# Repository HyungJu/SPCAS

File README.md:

# SPCAS
SmartPencilCase Application, PCB Design

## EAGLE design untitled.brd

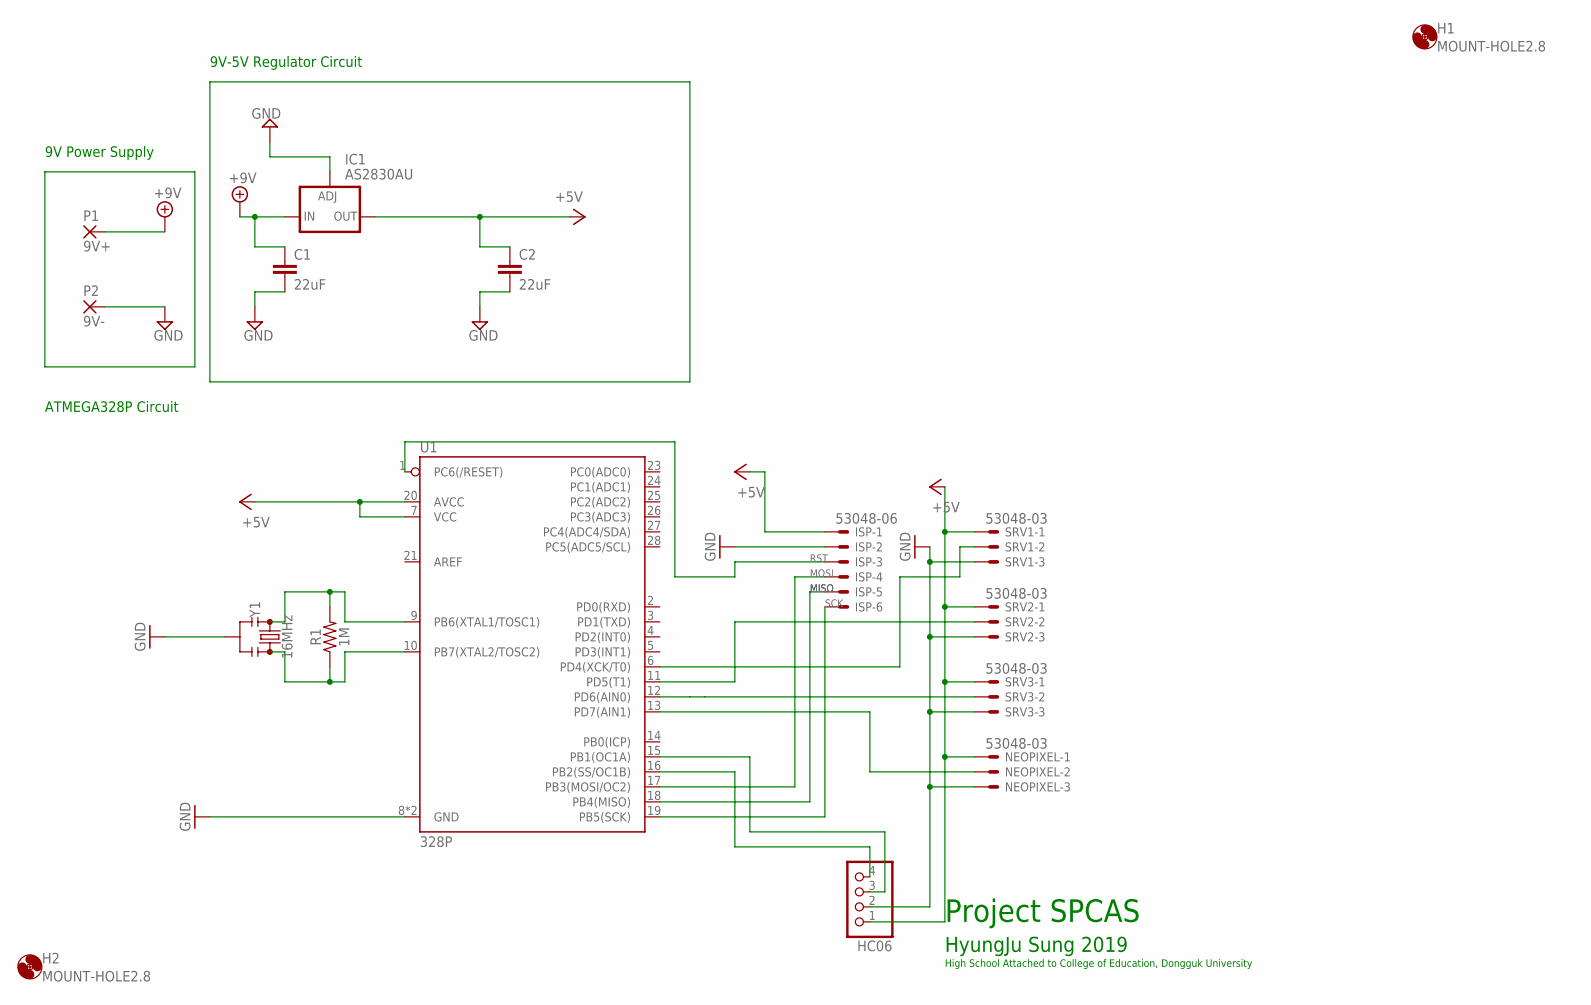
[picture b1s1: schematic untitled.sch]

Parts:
C1, C2: 22uF; C2.5-2
H1, H2: MOUNT-HOLE2.8; 2,8
HC06: PINHD-1X4/90; 1X04/90
IC1: AS2830AU; 337TL
ISP: 53048-06
NEOPIXEL: 53048-03
P1: 9V+; SMD2,54-5,08
P2: 9V-; SMD2,54-5,08
R1: 1M; AXIAL-0.3
SRV1, SRV2, SRV3: 53048-03
U1: 328P; DIP28
Y1: 16MHz; RESONATOR-SMD-3.2X1.3

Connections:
+5V: C2.1, HC06.1, IC1.3 (OUT), ISP.1, NEOPIXEL.1, SRV1.1, SRV2.1, SRV3.1, U1.7 (VCC), U1.20 (AVCC)
+9V: C1.1, IC1.2 (IN), P1.1
GND: C1.2, C2.2, HC06.2, IC1.1 (ADJ), ISP.2, NEOPIXEL.3, P2.1, SRV1.3, SRV2.3, SRV3.3, U1.8 (GND), U1.22 (GND), Y1.2
MISO: ISP.5, U1.18 (PB4(MISO))
MOSI: ISP.4, U1.17 (PB3(MOSI/OC2))
unnamed: R1.P$2 (2), U1.9 (PB6(XTAL1/TOSC1)), Y1.1
unnamed: R1.P$1 (1), U1.10 (PB7(XTAL2/TOSC2)), Y1.3
unnamed: NEOPIXEL.2, U1.13 (PD7(AIN1))
unnamed: SRV3.2, U1.12 (PD6(AIN0))
unnamed: SRV2.2, U1.11 (PD5(T1))
unnamed: SRV1.2, U1.6 (PD4(XCK/T0))
unnamed: HC06.4, U1.16 (PB2(SS/OC1B))
unnamed: HC06.3, U1.15 (PB1(OC1A))
RST: ISP.3, U1.1 (PC6(/RESET))
SCK: ISP.6, U1.19 (PB5(SCK))

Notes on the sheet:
9V Power Supply
9V-5V Regulator Circuit
ATMEGA328P Circuit
Project SPCAS
HyungJu Sung 2019
High School Attached to College of Education, Dongguk University

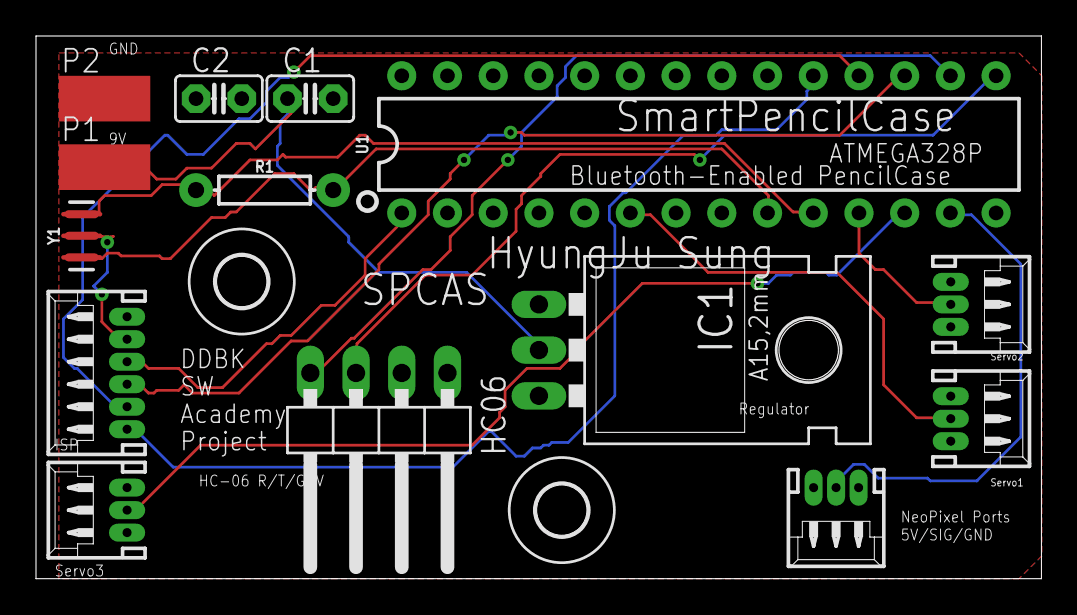
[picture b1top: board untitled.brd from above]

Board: 2 copper layers, 55.9 x 30.2 mm, 16 parts (0 on the bottom side), 15 nets.

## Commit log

2020-01-16 Uploaded PCB Artworks

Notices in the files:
parts and their libraries:
SparkFun-Resistors: Licensing: Creative Commons ShareAlike 4.0 International - https://creativecommons.org/licenses/by-sa/4.0
